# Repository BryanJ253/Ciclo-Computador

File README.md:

# Ciclo computador
Un dispositivo para promover la actividad fisica en bicicleta.
## Integrantes:
* Manuel Santiago Bastidas Gaona
* Bryan Felipe Jaime Diaz

# Introducción
En los últimos años e incrementado por el paso de la pandemia, las personas tienden a ser mas sedentarias, al estar sentadas mucho tiempo, sin realizar mucho movimiento, y se sabe que para tener buena salud se debe ser activo realizar actividad física para mantenerse en forma y evitar enfermedades y que mejor forma de realizar actividad física que en una bicicleta, se puede usar como medio de transporte para ir hacia el trabajo y volver a casa, y ya se esta realizando una cantidad de actividad física considerable y que claramente es mejor que nada por lo que se busca promover el uso de la bicicleta de la siguiente manera. Se plantea realizar este dispositivo dado que así podemos ayudar a las personas que usan una bicicleta, ya sea para su transporte diario, o para salir ocasionalmente a hacer deporte, a monitorear sus recorridos, y así llevar un seguimiento de la actividad física que están realizando, además que llevando este seguimiento se impulsa a la persona a realizar mas actividad física, ya que añade un grado progreso, al evidenciar cuando al cabo del tiempo la persona realiza los recorridos en un menor tiempo, o realiza recorridos mas largos.
Para la realización del dispositivo se siguen las fases adecuadas para su desarrollo, desde empezar a crear diagramas que nos dieran un idea general de lo que iba a ser el proyecto, realizar diagramas mas avanzados implementando los componentes que contendrá el dispositivo, hasta la realización misma del dispositivo, realizando el sistema electrónico e implementando una PCB para el ensamble de los componentes electrónicos, hasta la realización de una caja donde se acomode todo este sistema electrónico.

Palabras clave: Bicicleta, actividad física, persona, deporte, tiempo, dispositivo.
# Poster

# Banner

# Video del CicloComputador
### En este video se abordan los siguientes aspectos:
* La problemática
* La solución planteada (los módulos usados)
* El funcionamiento explicado tecnicamente
* El funcionamiento del proyecto desde el punto de vista del usuario

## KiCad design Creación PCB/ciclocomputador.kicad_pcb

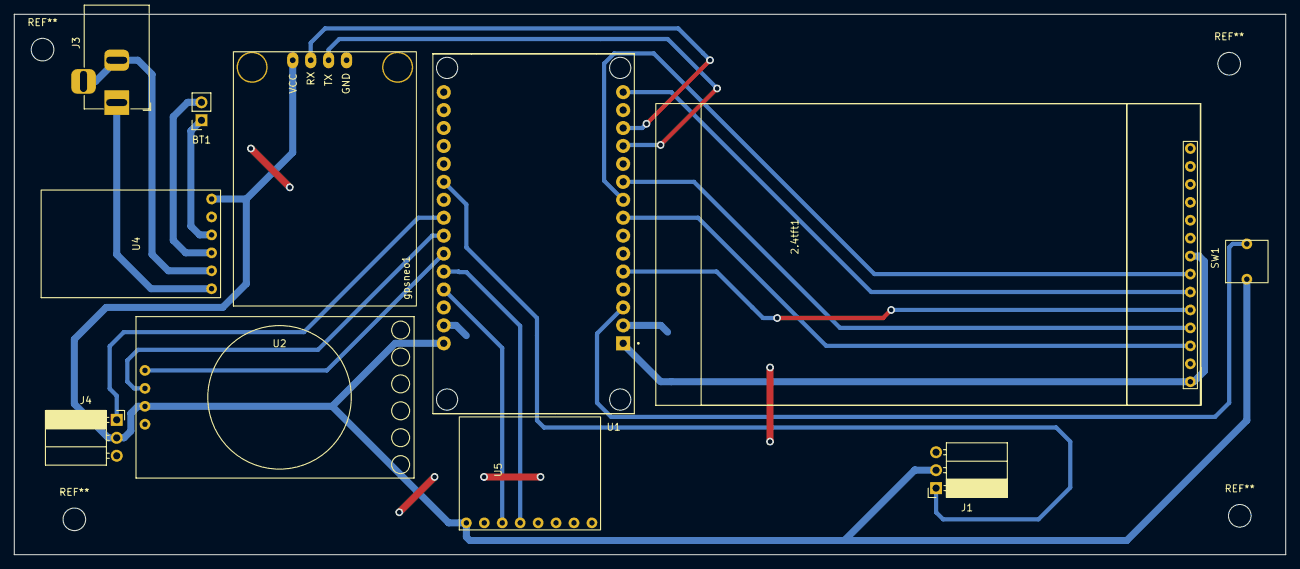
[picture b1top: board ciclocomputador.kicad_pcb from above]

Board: 2 copper layers, 180.0 x 76.5 mm, 11 parts (0 on the bottom side), 19 nets.

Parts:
2.4tft1: pantalla sencilla
BT1: Battery; PinSocket_1x02_P2.54mm_Vertical
J1, J4: Conn_01x03_Socket; PinSocket_1x03_P2.54mm_Horizontal
J3: Barrel_Jack_Switch; BarrelJack_Horizontal
SW1: SW_Push; boton
U1: ESP32-DEVKIT-V1; MODULE_ESP32_DEVKIT_V1
U2: TC00500; RTC_DS3231
U4: mh-cd42
U5: mpu6050
gpsneo1: GY-NEO6MV2

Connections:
+3V3: 2.4tft1.1 (VIN), 2.4tft1.8 (LED), U1.1 (3V3)
+5V: J1.2, J4.2, SW1.2, U1.30 (VIN), U2.2 (VCC), U4.6 (OUT-5V), U5.1 (vcc), gpsneo1.1 (vcc)
+BATT: BT1.1 (+), U4.4 (BAT)
/ds3231-scl: U1.25 (D27), U2.4 (SCL)
/ds3231-sda: U1.24 (D26), U2.3 (SDA)
/gps-16: U1.13 (TX0), gpsneo1.2 (rx)
/hall1: J4.1, U1.23 (D25)
/hall2: J1.1, U1.21 (D32)
/mpu-scl: U1.27 (D12), U5.3 (scl)
/mpu-sda: U1.26 (D14), U5.4 (sda)
/pantalla mosi: 2.4tft1.6 (SDI(MOSI)), U1.15 (D23)
/pantalla reset: 2.4tft1.4 (RESET), U1.10 (D19)
/pantalla_cs: 2.4tft1.3 (CS), U1.8 (D5)
/pantalla_dc: 2.4tft1.5 (D/C), U1.5 (D4)
/pantalla_sck(sclk): 2.4tft1.7 (SCK), U1.9 (D18)
GND: 2.4tft1.2 (GND), BT1.2 (-), J1.3, J3.2, J3.3, J4.3, U1.2 (GND), U1.29 (GND), U2.1 (GND), U4.2 (GND), U4.3 (GND), U4.5 (GND), U5.2 (gnd), gpsneo1.4 (gnd)
unnamed: SW1.1, U1.3 (D15)
unnamed: U1.12 (RX0), gpsneo1.3 (tx)
VDC: J3.1, U4.1 (VIN)

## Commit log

2024-09-27 Create pcb
2024-09-27 Create Imágenes del proceso
2024-09-27 Create borrar
2024-09-27 Create ima
2024-09-27 Create img
2024-09-27 Rename Ciclo computador.jpg to Banner.jpg
2024-09-27 Rename image.jpg to PCB_symbol.jpg
2024-09-27 Rename PCB.jpg to PCB_footprint.jpg
2024-09-27 Create Creación PCB
2024-09-27 Create borra
2024-09-27 Create borr
2024-09-27 Rename Codigon 2.jfif to codigo_funcionamiento.jfif
2024-09-27 Rename Codigo 1.jfif to Proceso_codigo.jfif
